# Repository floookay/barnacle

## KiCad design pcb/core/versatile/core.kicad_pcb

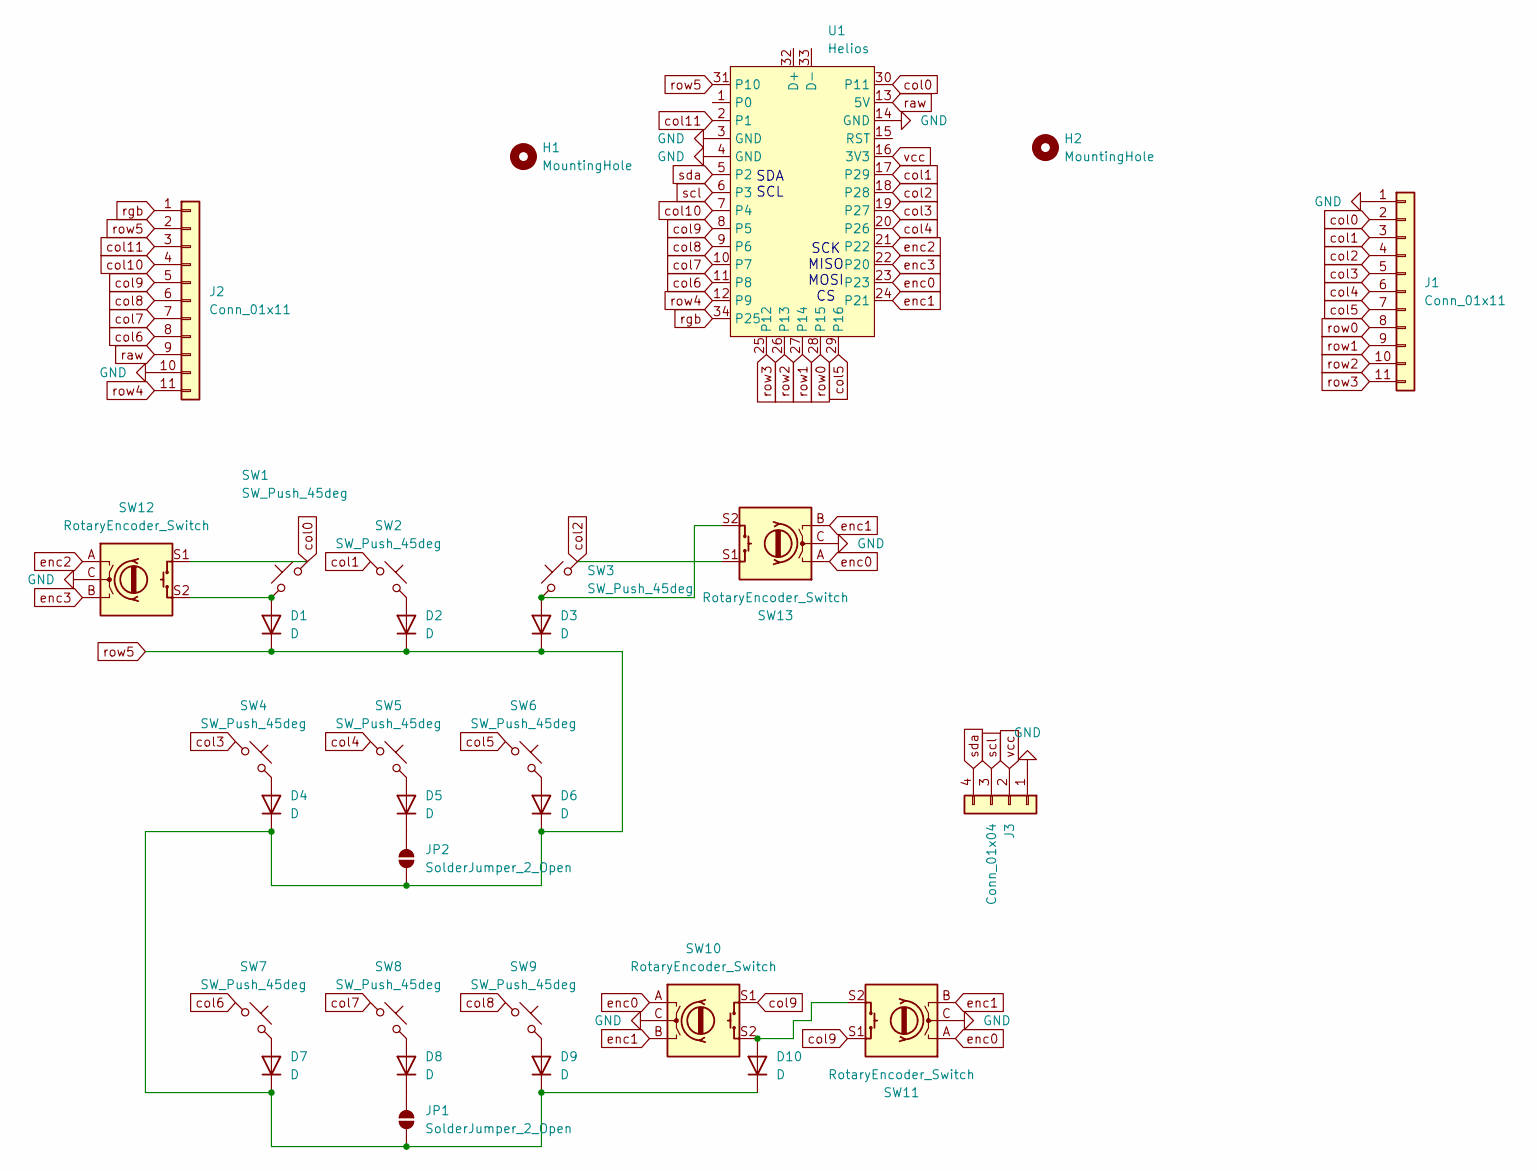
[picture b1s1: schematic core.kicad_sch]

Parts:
D1, D2, D3, D4, D5, D6, D7, D8, D9, D10: D; D_SOD-123
H1, H2: MountingHole; MountingHole_3.2mm_M3_DIN965_Pad
J1, J2: Conn_01x11; PinHeader_1x11_P2.54mm_Vertical
J3: Conn_01x04; PinHeader_1x04_P2.54mm_Vertical
JP1, JP2: SolderJumper_2_Open; SolderJumper-2_P1.3mm_Open_RoundedPad1.0x1.5mm
SW1, SW2, SW3, SW4, SW5, SW6, SW7, SW8, SW9: SW_Push_45deg; SW_MX_1u
SW10, SW11, SW12, SW13: RotaryEncoder_Switch; ROT_Alps_EC11E-Switch
U1: Helios; Helios_AH_USBup

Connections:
GND: J1.1, J2.10, J3.1, SW10.C, SW11.C, SW12.C, SW13.C, U1.3 (GND), U1.4 (GND), U1.14 (GND)
unnamed: D1.2 (A), SW1.1, SW12.S2
unnamed: D2.2 (A), SW2.2
unnamed: D3.2 (A), SW3.1, SW13.S2
unnamed: D4.2 (A), SW4.2
unnamed: D5.2 (A), SW5.2
unnamed: D5.1 (K), JP2.1 (A)
unnamed: D6.2 (A), SW6.2
unnamed: D7.2 (A), SW7.2
unnamed: D8.2 (A), SW8.2
unnamed: D8.1 (K), JP1.1 (A)
unnamed: D9.2 (A), SW9.2
unnamed: D10.2 (A), SW10.S2, SW11.S2
unnamed 13: U1.1 (P0); also elsewhere on the board
col0: J1.2, SW1.2, SW12.S1, U1.30 (P11)
col1: J1.3, SW2.1, U1.17 (P29)
col2: J1.4, SW3.2, SW13.S1, U1.18 (P28)
col3: J1.5, SW4.1, U1.19 (P27)
col4: J1.6, SW5.1, U1.20 (P26)
col5: J1.7, SW6.1, U1.29 (P16)
col6: J2.8, SW7.1, U1.11 (P8)
col7: J2.7, SW8.1, U1.10 (P7)
col8: J2.6, SW9.1, U1.9 (P6)
col9: J2.5, SW10.S1, SW11.S1, U1.8 (P5)
col10: J2.4, U1.7 (P4)
col11: J2.3, U1.2 (P1)
enc0: SW10.A, SW11.A, SW13.A, U1.23
enc1: SW10.B, SW11.B, SW13.B, U1.24 (P21)
enc2: SW12.A, U1.21 (P22)
enc3: SW12.B, U1.22 (P20)
row0: J1.8, U1.28 (P15)
row1: J1.9, U1.27 (P14)
row2: J1.10, U1.26 (P13)
row3: J1.11, U1.25 (P12)
row4: J2.11, U1.12 (P9)
row5: D1.1 (K), D2.1 (K), D3.1 (K), D4.1 (K), D6.1 (K), D7.1 (K), D9.1 (K), D10.1 (K), J2.2, JP1.2 (B), JP2.2 (B), U1.31 (P10)
scl: J3.3, U1.6 (P3)
sda: J3.4, U1.5 (P2)
vcc: J3.2, U1.16 (3V3); also elsewhere on the board

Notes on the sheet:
SDA SCL
SCK MISO MOSI CS

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
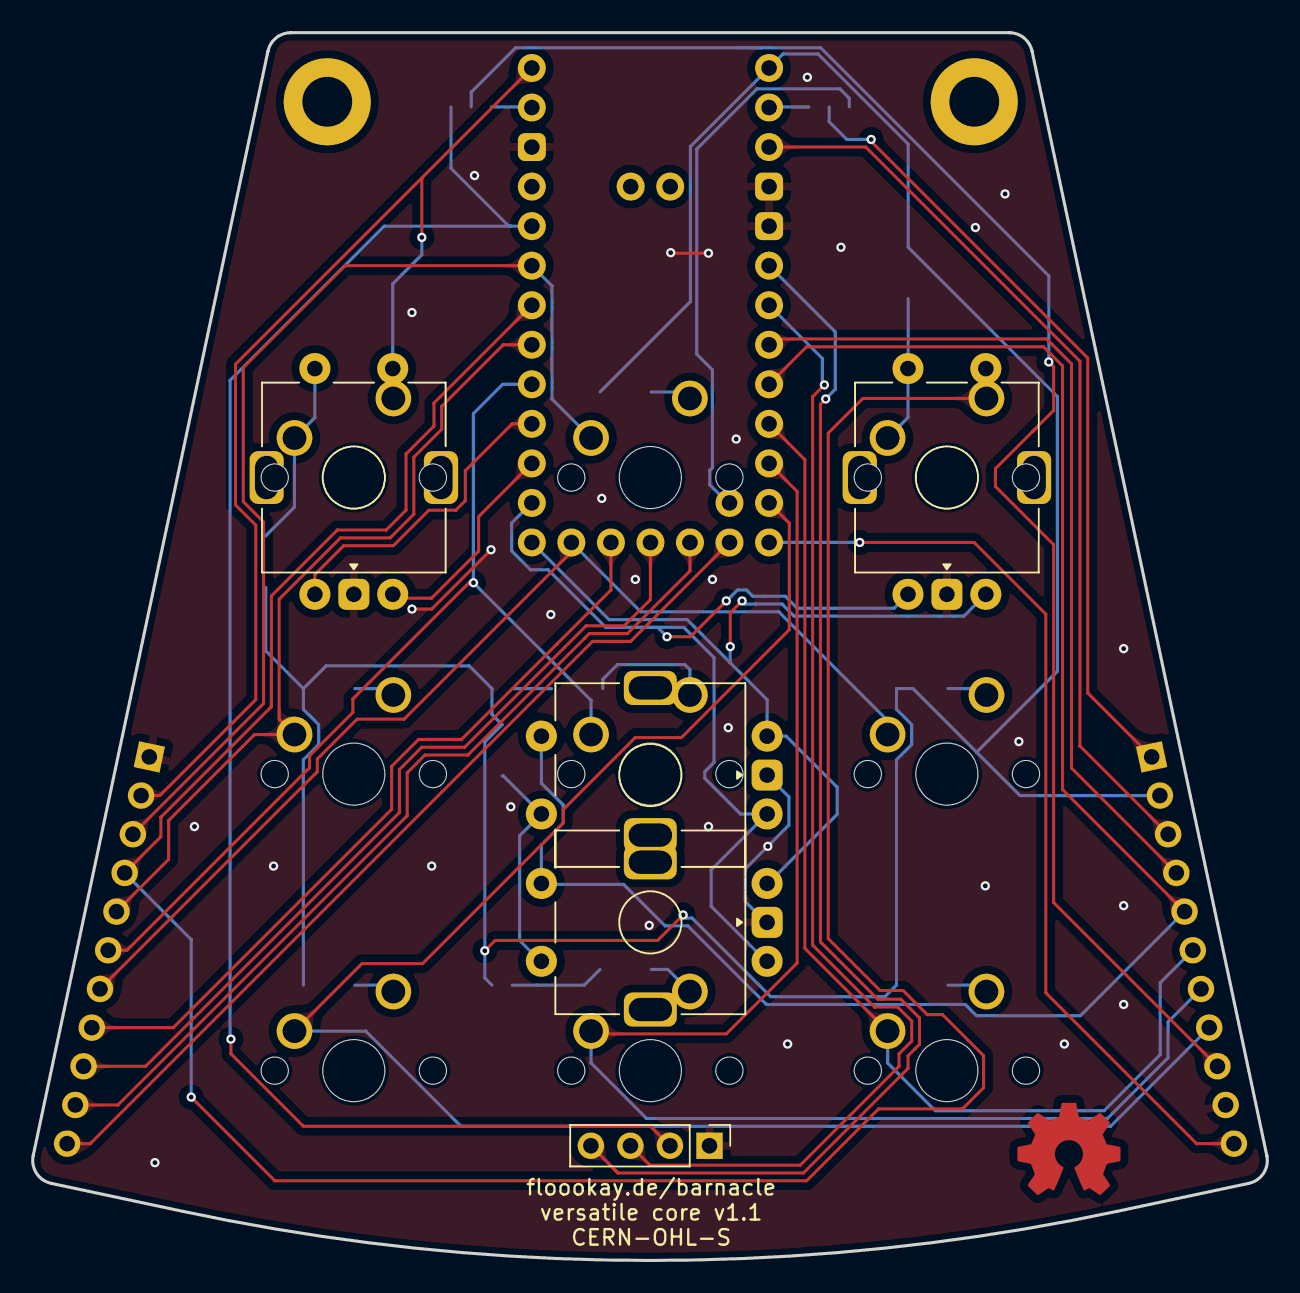
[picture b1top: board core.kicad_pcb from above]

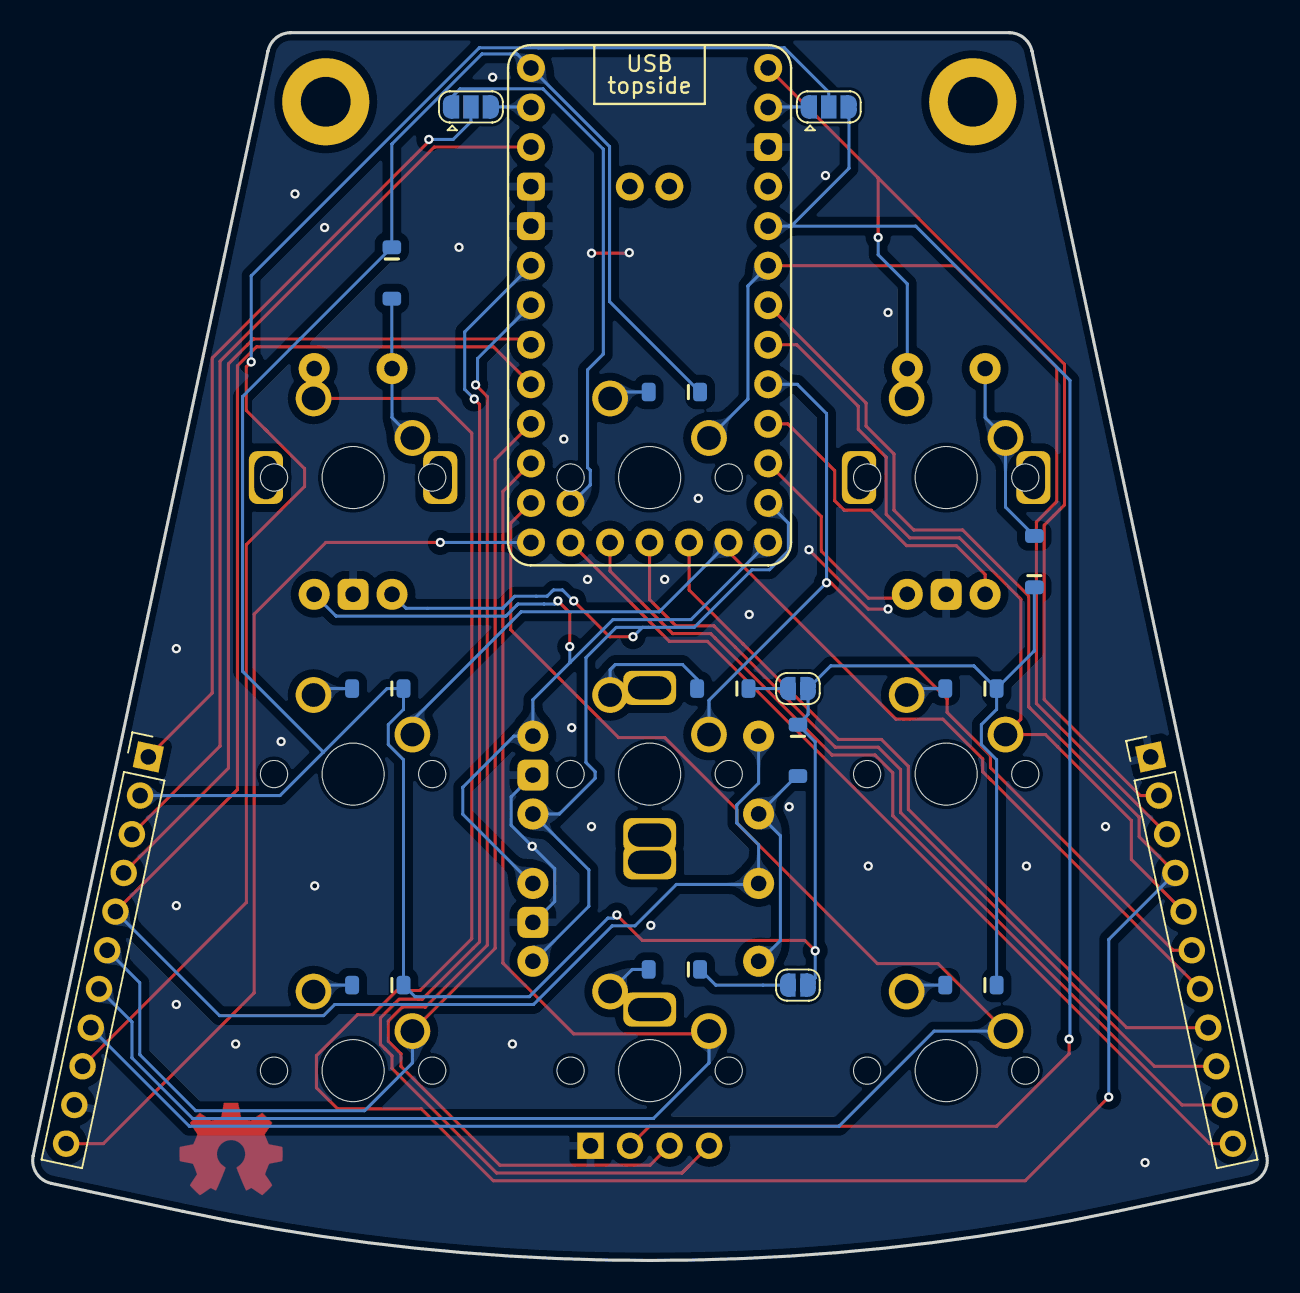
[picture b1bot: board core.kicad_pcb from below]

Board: 2 copper layers, 79.3 x 78.9 mm, 33 parts (17 on the bottom side), 43 nets.

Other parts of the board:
JP3, JP4: Jumper_3_Open; SolderJumper-3_P1.3mm_Open_RoundedPad1.0x1.5mm

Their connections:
unnamed 13: JP3.3 (B); also elsewhere on the board
vcc: JP4.3 (B); also elsewhere on the board

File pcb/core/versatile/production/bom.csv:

Designator,Footprint,Quantity,Value,LCSC Part #
"D1, D10, D2, D3, D4, D5, D6, D7, D8, D9",D_SOD-123-minimal,10,D,
"J1, J2",PinHeader_1x11_P2.54mm_Vertical,2,Conn_01x11,
J3,PinHeader_1x04_P2.54mm_Vertical,1,Conn_01x04,
"SW1, SW2, SW3, SW4, SW5, SW6, SW7, SW8, SW9",SW_MX_1u,9,SW_Push_45deg,
"SW10, SW11, SW12, SW13",ROT_Alps_EC11E-Switch,4,RotaryEncoder_Switch,

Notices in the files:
pcb/core/versatile/core.kicad_pcb:
CERN-OHL-S
